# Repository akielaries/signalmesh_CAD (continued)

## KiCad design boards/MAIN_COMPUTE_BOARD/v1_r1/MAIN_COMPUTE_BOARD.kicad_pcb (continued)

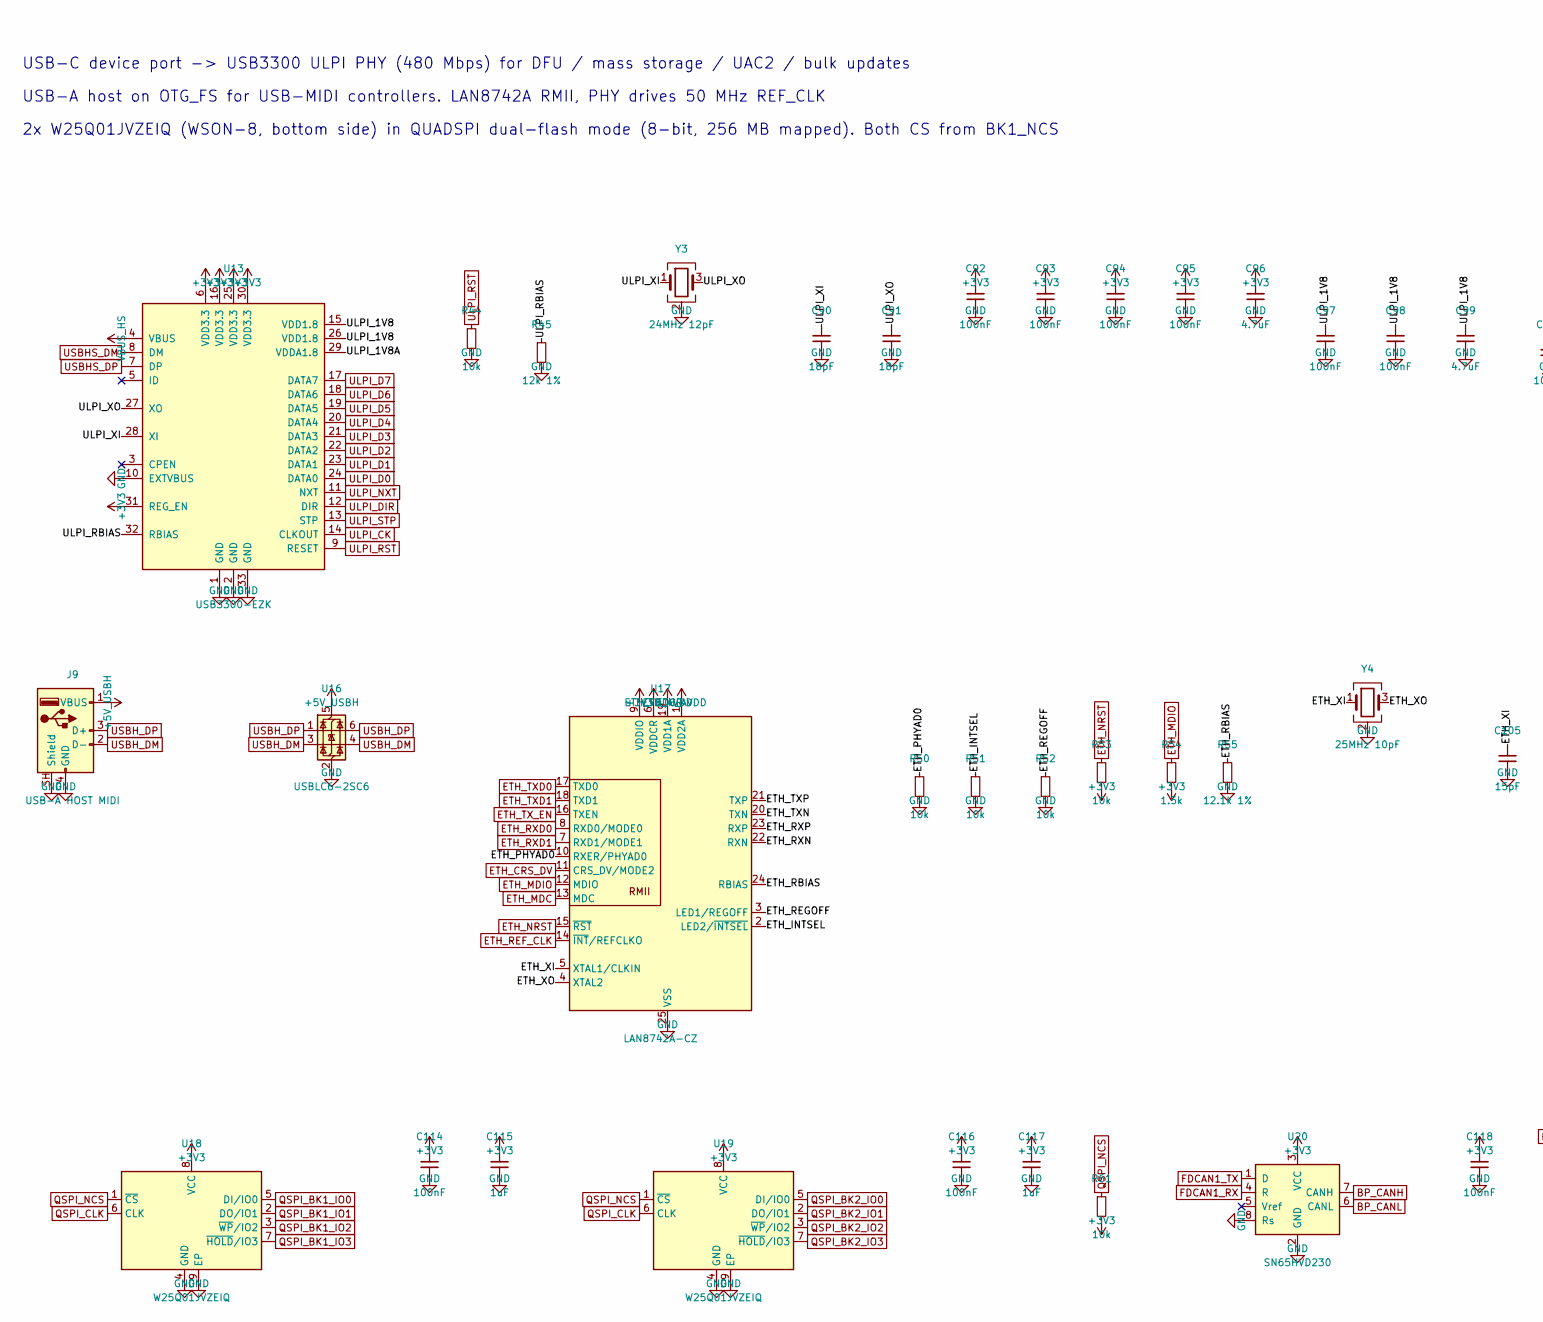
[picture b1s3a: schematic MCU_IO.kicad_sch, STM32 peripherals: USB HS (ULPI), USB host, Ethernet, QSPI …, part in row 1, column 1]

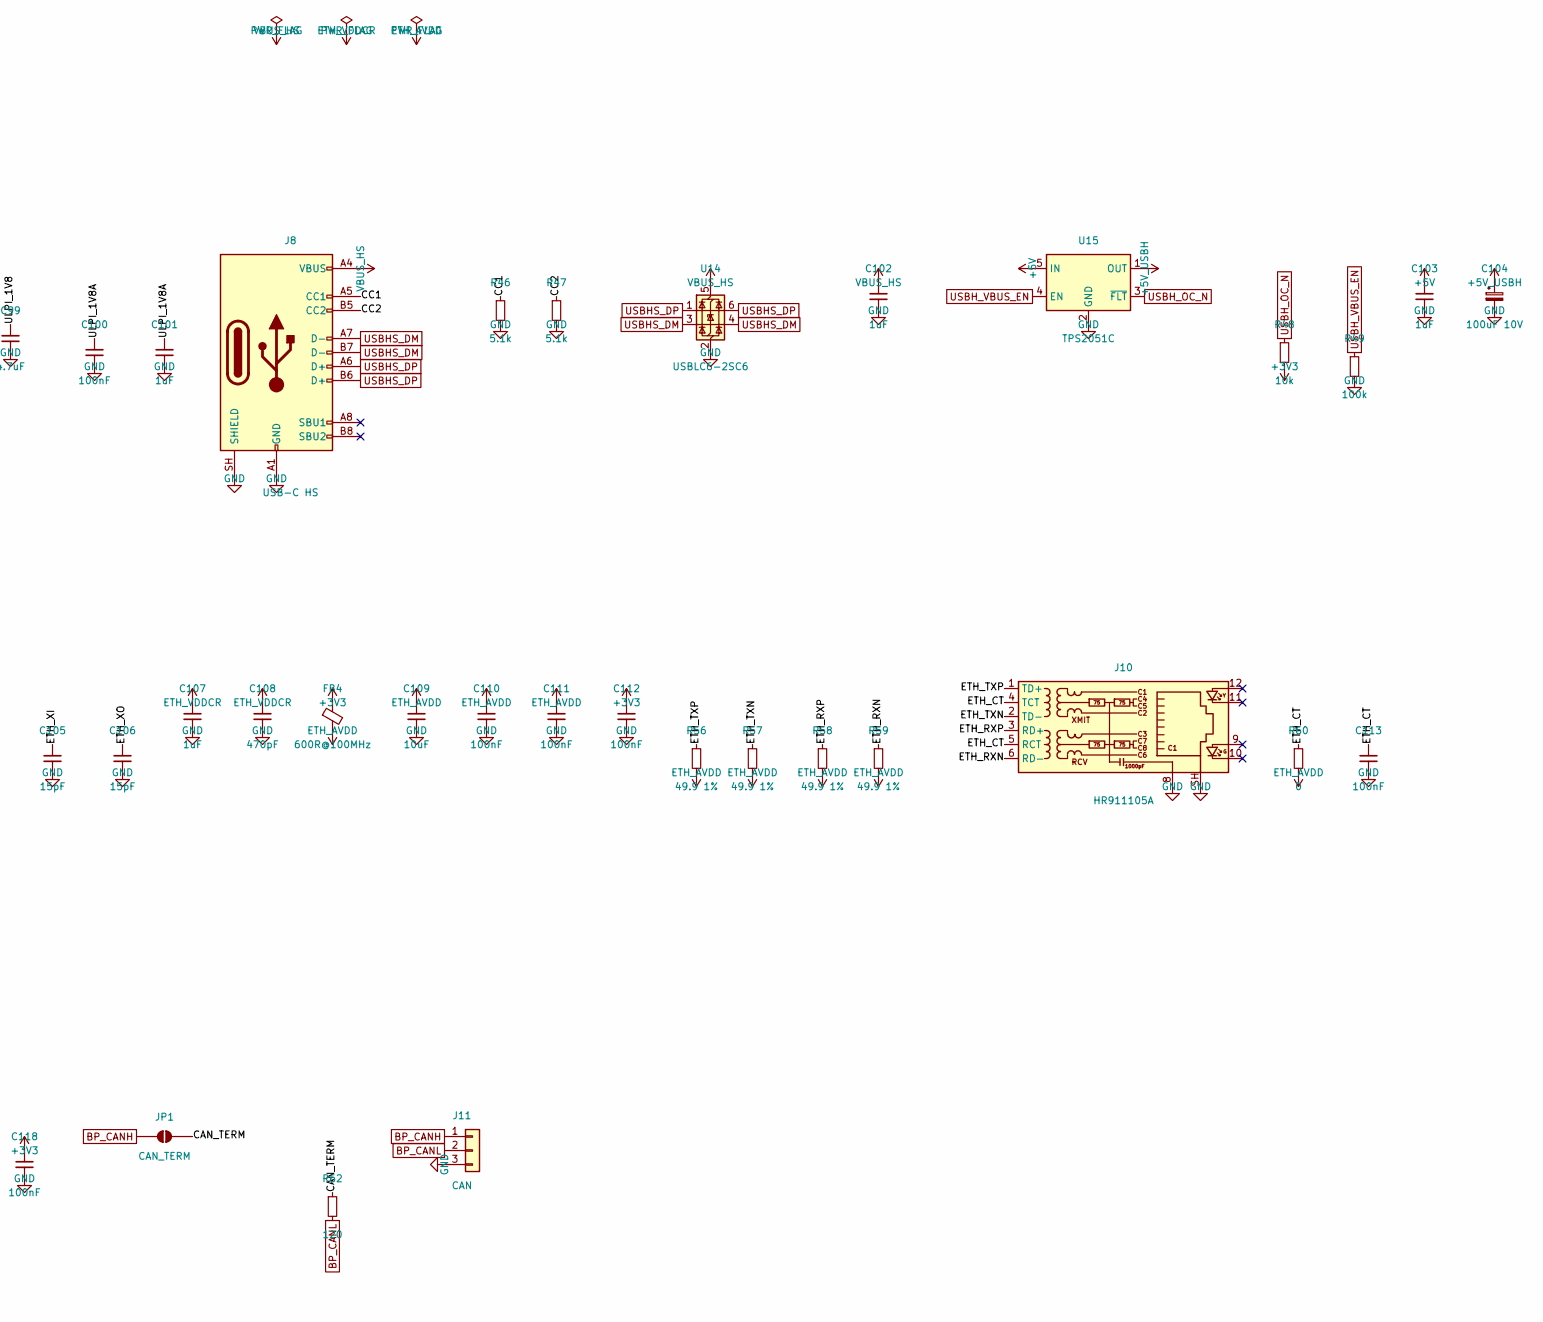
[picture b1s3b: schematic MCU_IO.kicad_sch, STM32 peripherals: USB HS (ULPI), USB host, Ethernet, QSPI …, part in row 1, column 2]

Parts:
C90, C91: 18pF; C_0402_1005Metric
C92, C93, C94, C95, C97, C98, C100, C110, C111, C112, C113, C114, C116, C118: 100nF; C_0402_1005Metric
C96, C99: 4.7uF; C_0603_1608Metric
C101, C102, C103, C107, C115, C117: 1uF; C_0402_1005Metric
C104: 100uF 10V; CP_Elec_6.3x7.7
C105, C106: 15pF; C_0402_1005Metric
C108: 470pF; C_0402_1005Metric
C109: 10uF; C_0805_2012Metric
FB4: 600R@100MHz; L_0603_1608Metric
J8: USB-C HS; USB_C_Receptacle_HRO_TYPE-C-31-M-12
J9: USB-A HOST MIDI; USB_A_Molex_67643_Horizontal
J10: HR911105A; RJ45_Hanrun_HR911105A_Horizontal
J11: CAN; PinHeader_1x03_P2.54mm_Vertical
JP1: CAN_TERM; SolderJumper-2_P1.3mm_Open_RoundedPad1.0x1.5mm
R44, R48, R50, R51, R52, R53, R61: 10k; R_0402_1005Metric
R45: 12k 1%; R_0402_1005Metric
R46, R47: 5.1k; R_0402_1005Metric
R49: 100k; R_0402_1005Metric
R54: 1.5k; R_0402_1005Metric
R55: 12.1k 1%; R_0402_1005Metric
R56, R57, R58, R59: 49.9 1%; R_0402_1005Metric
R60: 0; R_0402_1005Metric
R62: 120; R_0402_1005Metric
U13: USB3300-EZK; QFN-32-1EP_5x5mm_P0.5mm_EP3.45x3.45mm
U14, U16: USBLC6-2SC6; SOT-23-6
U15: TPS2051C; SOT-23-5
U17: LAN8742A-CZ; VQFN-24-1EP_4x4mm_P0.5mm_EP2.5x2.5mm_ThermalVias
U18, U19: W25Q01JVZEIQ; WSON-8-1EP_8x6mm_P1.27mm_EP3.4x4.3mm; LCSC C6926235
U20: SN65HVD230; SOIC-8_3.9x4.9mm_P1.27mm
Y3: 24MHz 12pF; Crystal_SMD_3225-4Pin_3.2x2.5mm
Y4: 25MHz 10pF; Crystal_SMD_3225-4Pin_3.2x2.5mm

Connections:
+3V3: C92.1, C93.1, C94.1, C95.1, C96.1, C112.1, C114.1, C115.1, C116.1, C117.1, C118.1, FB4.1, R48.2, R53.2, R54.2, R61.2, U13.6 (VDD3.3), U13.16 (VDD3.3), U13.25 (VDD3.3), U13.30 (VDD3.3), U13.31 (REG_EN), U17.9 (VDDIO), U18.8 (VCC), U19.8 (VCC), U20.3 (VCC); also elsewhere on the board
+5V: C103.1, U15.5 (IN); also elsewhere on the board
+5V_USBH: C104.1, J9.1 (VBUS), U15.1 (OUT), U16.5 (VBUS)
/MCU_IO/CAN_TERM: JP1.2 (B), R62.1
/MCU_IO/CC1: J8.A5 (CC1), R46.1
/MCU_IO/CC2: J8.B5 (CC2), R47.1
/MCU_IO/ETH_CT: C113.1, J10.4 (TCT), J10.5 (RCT), R60.1
/MCU_IO/ETH_INTSEL: R51.1, U17.2 (LED2/~INTSEL)
/MCU_IO/ETH_PHYAD0: R50.1, U17.10 (RXER/PHYAD0)
/MCU_IO/ETH_RBIAS: R55.1, U17.24 (RBIAS)
/MCU_IO/ETH_REGOFF: R52.1, U17.3 (LED1/REGOFF)
/MCU_IO/ETH_RXN: J10.6 (RD-), R59.1, U17.22 (RXN)
/MCU_IO/ETH_RXP: J10.3 (RD+), R58.1, U17.23 (RXP)
/MCU_IO/ETH_TXN: J10.2 (TD-), R57.1, U17.20 (TXN)
/MCU_IO/ETH_TXP: J10.1 (TD+), R56.1, U17.21 (TXP)
/MCU_IO/ETH_XI: C105.1, U17.5 (XTAL1/CLKIN), Y4.1
/MCU_IO/ETH_XO: C106.1, U17.4 (XTAL2), Y4.3
/MCU_IO/ULPI_1V8: C97.1, C98.1, C99.1, U13.15 (VDD1.8), U13.26 (VDD1.8)
/MCU_IO/ULPI_1V8A: C100.1, C101.1, U13.29 (VDDA1.8)
/MCU_IO/ULPI_RBIAS: R45.1, U13.32 (RBIAS)
/MCU_IO/ULPI_XI: C90.1, U13.28 (XI), Y3.1
/MCU_IO/ULPI_XO: C91.1, U13.27 (XO), Y3.3
BP_CANH: J11.1, JP1.1 (A), U20.7 (CANH); also elsewhere on the board
BP_CANL: J11.2, R62.2, U20.6 (CANL); also elsewhere on the board
ETH_AVDD: C109.1, C110.1, C111.1, FB4.2, R56.2, R57.2, R58.2, R59.2, R60.2, U17.1 (VDD2A), U17.19 (VDD1A)
ETH_CRS_DV: U17.11 (CRS_DV/MODE2); also elsewhere on the board
ETH_MDC: U17.13 (MDC); also elsewhere on the board
ETH_MDIO: R54.1, U17.12 (MDIO); also elsewhere on the board
ETH_NRST: R53.1, U17.15 (~RST); also elsewhere on the board
ETH_REF_CLK: U17.14 (~INT/REFCLKO); also elsewhere on the board
ETH_RXD0: U17.8 (RXD0/MODE0); also elsewhere on the board
ETH_RXD1: U17.7 (RXD1/MODE1); also elsewhere on the board
ETH_TXD0: U17.17 (TXD0); also elsewhere on the board
ETH_TXD1: U17.18 (TXD1); also elsewhere on the board
ETH_TX_EN: U17.16 (TXEN); also elsewhere on the board
ETH_VDDCR: C107.1, C108.1, U17.6 (VDDCR)
FDCAN1_RX: U20.4 (R); also elsewhere on the board
FDCAN1_TX: U20.1 (D); also elsewhere on the board
GND: C90.2, C91.2, C92.2, C93.2, C94.2, C95.2, C96.2, C97.2, C98.2, C99.2, C100.2, C101.2, C102.2, C103.2, C104.2, C105.2, C106.2, C107.2, C108.2, C109.2, C110.2, C111.2, C112.2, C113.2, C114.2, C115.2, C116.2, C117.2, C118.2, J8.A1 (GND), J8.A12 (GND), J8.B1 (GND), J8.B12 (GND), J8.SH (SHIELD), J9.4 (GND), J9.SH (Shield), J10.8, J10.SH, J11.3, R44.2, R45.2, R46.2, R47.2, R49.2, R50.2, R51.2, R52.2, R55.2, U13.1 (GND), U13.2 (GND), U13.10 (EXTVBUS), U13.33 (GND), U14.2 (GND), U15.2 (GND), U16.2 (GND), U17.25 (VSS), U18.4 (GND), U18.9 (EP), U19.4 (GND), U19.9 (EP), U20.2 (GND), U20.8 (Rs), Y3.2 (G), Y3.4 (G), Y4.2 (G), Y4.4 (G); also elsewhere on the board
QSPI_BK1_IO0: U18.5 (DI/IO0); also elsewhere on the board
QSPI_BK1_IO1: U18.2 (DO/IO1); also elsewhere on the board
QSPI_BK1_IO2: U18.3 (~WP/IO2); also elsewhere on the board
QSPI_BK1_IO3: U18.7 (~HOLD/IO3); also elsewhere on the board
QSPI_BK2_IO0: U19.5 (DI/IO0); also elsewhere on the board
QSPI_BK2_IO1: U19.2 (DO/IO1); also elsewhere on the board
QSPI_BK2_IO2: U19.3 (~WP/IO2); also elsewhere on the board
QSPI_BK2_IO3: U19.7 (~HOLD/IO3); also elsewhere on the board
QSPI_CLK: U18.6 (CLK), U19.6 (CLK); also elsewhere on the board
QSPI_NCS: R61.1, U18.1 (~CS), U19.1 (~CS); also elsewhere on the board
ULPI_CK: U13.14 (CLKOUT); also elsewhere on the board
ULPI_D0: U13.24 (DATA0); also elsewhere on the board
ULPI_D1: U13.23 (DATA1); also elsewhere on the board
ULPI_D2: U13.22 (DATA2); also elsewhere on the board
ULPI_D3: U13.21 (DATA3); also elsewhere on the board
ULPI_D4: U13.20 (DATA4); also elsewhere on the board
ULPI_D5: U13.19 (DATA5); also elsewhere on the board
ULPI_D6: U13.18 (DATA6); also elsewhere on the board
ULPI_D7: U13.17 (DATA7); also elsewhere on the board
ULPI_DIR: U13.12 (DIR); also elsewhere on the board
ULPI_NXT: U13.11 (NXT); also elsewhere on the board
ULPI_RST: R44.1, U13.9 (RESET); also elsewhere on the board
ULPI_STP: U13.13 (STP); also elsewhere on the board
USBHS_DM: J8.A7 (D-), J8.B7 (D-), U13.8 (DM), U14.3 (I/O2), U14.4 (I/O2)
USBHS_DP: J8.A6 (D+), J8.B6 (D+), U13.7 (DP), U14.1 (I/O1), U14.6 (I/O1)
USBH_DM: J9.2 (D-), U16.3 (I/O2), U16.4 (I/O2); also elsewhere on the board
USBH_DP: J9.3 (D+), U16.1 (I/O1), U16.6 (I/O1); also elsewhere on the board
USBH_OC_N: R48.1, U15.3 (~FLT); also elsewhere on the board
USBH_VBUS_EN: R49.1, U15.4 (EN); also elsewhere on the board
VBUS_HS: C102.1, J8.A4 (VBUS), J8.A9 (VBUS), J8.B4 (VBUS), J8.B9 (VBUS), U13.4 (VBUS), U14.5 (VBUS)

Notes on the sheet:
USB-C device port -> USB3300 ULPI PHY (480 Mbps) for DFU / mass storage / UAC2 / bulk updates
USB-A host on OTG_FS for USB-MIDI controllers. LAN8742A RMII, PHY drives 50 MHz REF_CLK
2x W25Q01JVZEIQ (WSON-8, bottom side) in QUADSPI dual-flash mode (8-bit, 256 MB mapped). Both CS from BK1_NCS

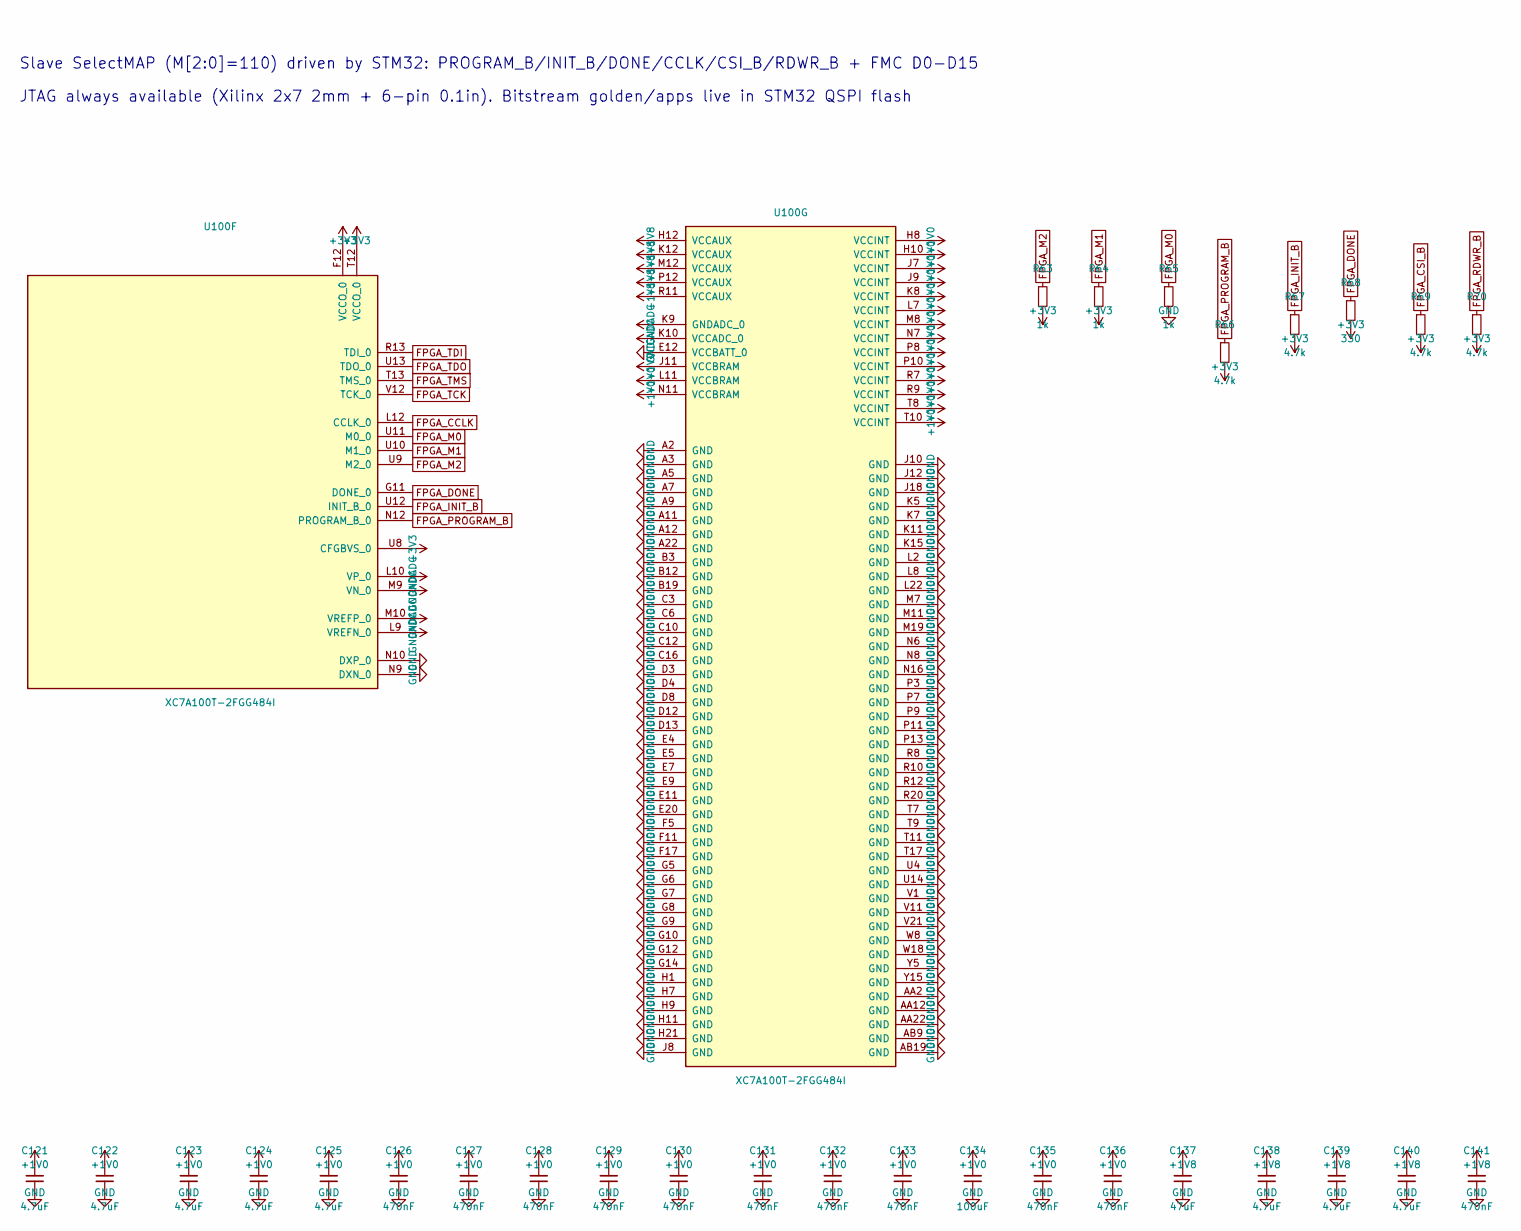
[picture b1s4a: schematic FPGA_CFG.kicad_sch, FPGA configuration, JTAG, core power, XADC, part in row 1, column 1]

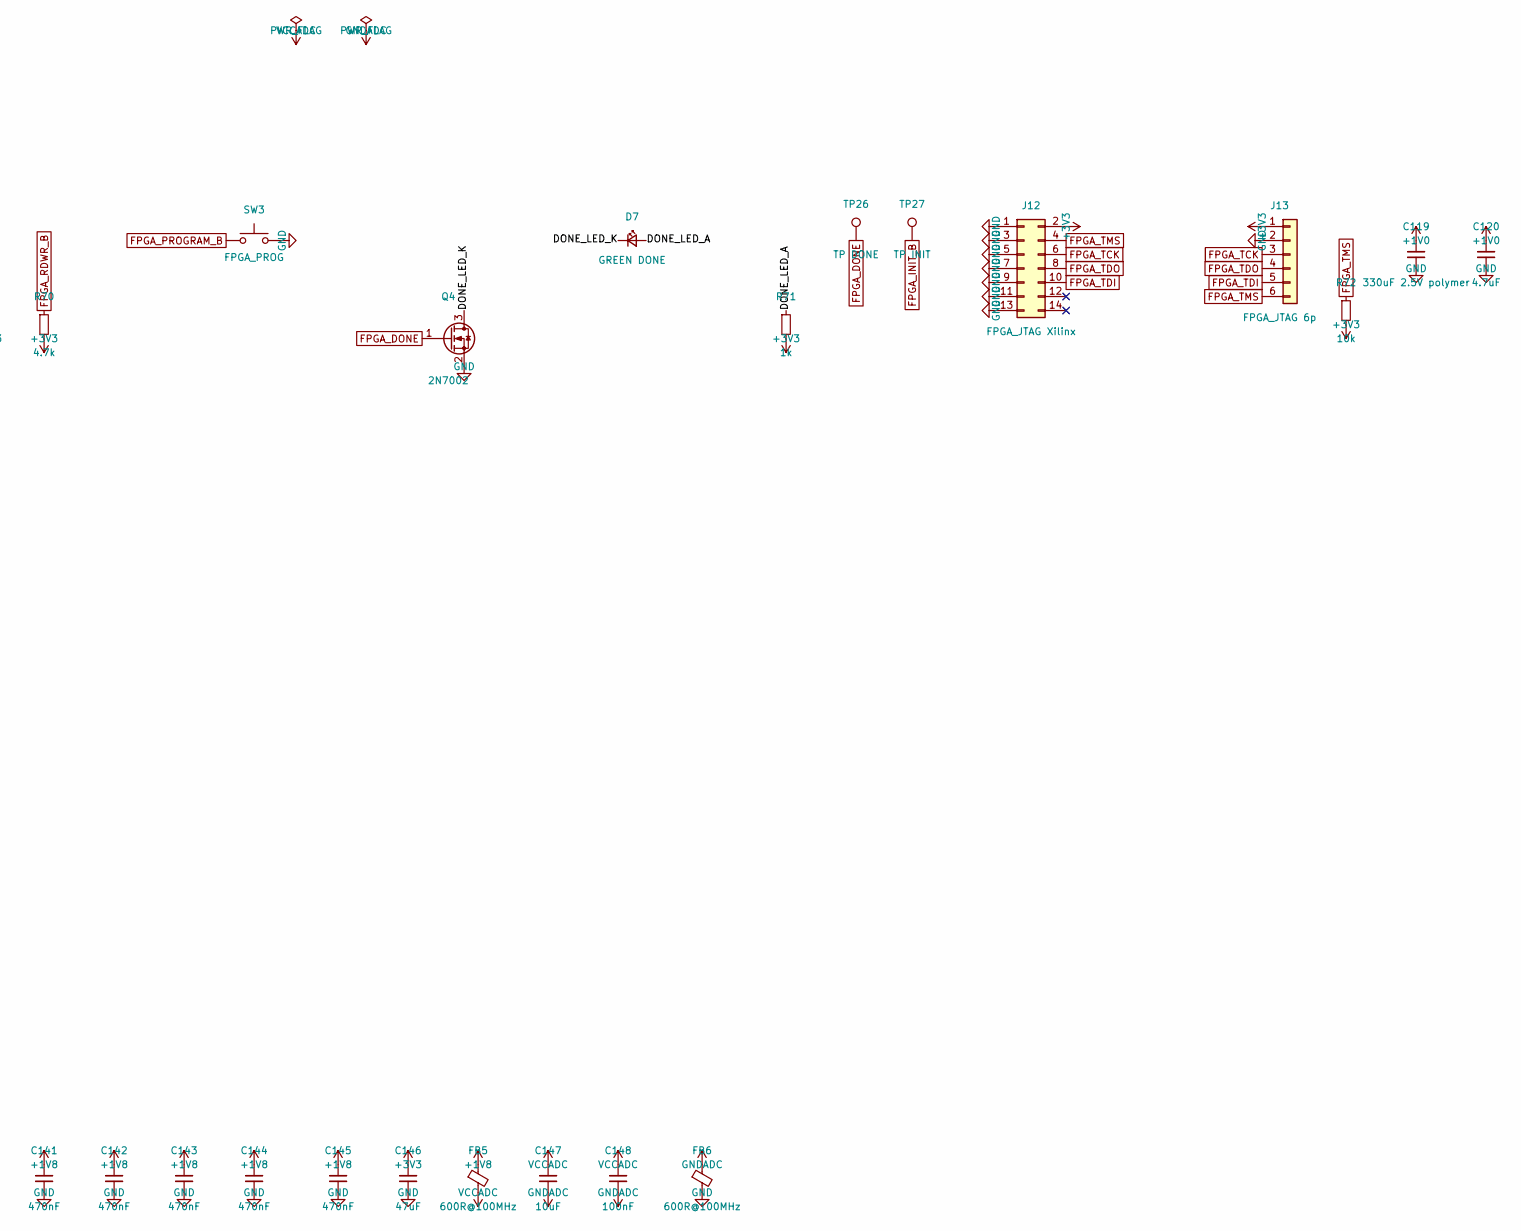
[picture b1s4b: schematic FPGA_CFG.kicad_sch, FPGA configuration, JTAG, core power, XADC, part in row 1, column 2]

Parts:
C119: 330uF 2.5V polymer; CP_EIA-7343-31_Kemet-D
C120, C121, C122, C123, C124, C125, C138, C139, C140: 4.7uF; C_0603_1608Metric
C126, C127, C128, C129, C130, C131, C132, C133, C135, C136, C141, C142, C143, C144, C145: 470nF; C_0402_1005Metric
C134: 100uF; C_1210_3225Metric
C137, C146: 47uF; C_1206_3216Metric
C147: 10uF; C_0805_2012Metric
C148: 100nF; C_0402_1005Metric
D7: GREEN DONE; LED_0603_1608Metric
FB5, FB6: 600R@100MHz; L_0603_1608Metric
J12: FPGA_JTAG Xilinx; PinHeader_2x07_P2.00mm_Vertical
J13: FPGA_JTAG 6p; PinHeader_1x06_P2.54mm_Vertical
Q4: 2N7002; SOT-23
R63, R64, R65, R71: 1k; R_0402_1005Metric
R66, R67, R69, R70: 4.7k; R_0402_1005Metric
R68: 330; R_0402_1005Metric
R72: 10k; R_0402_1005Metric
SW3: FPGA_PROG; SW_SPST_TL3342
TP26: TP DONE; TestPoint_Pad_D1.5mm
TP27: TP INIT; TestPoint_Pad_D1.5mm
U100: XC7A100T-2FGG484I; Xilinx_FGG484

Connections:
+1V0: C119.1, C120.1, C121.1, C122.1, C123.1, C124.1, C125.1, C126.1, C127.1, C128.1, C129.1, C130.1, C131.1, C132.1, C133.1, C134.1, C135.1, C136.1, U100.H8 (VCCINT), U100.H10 (VCCINT), U100.J7 (VCCINT), U100.J9 (VCCINT), U100.J11 (VCCBRAM), U100.K8 (VCCINT), U100.L7 (VCCINT), U100.L11 (VCCBRAM), U100.M8 (VCCINT), U100.N7 (VCCINT), U100.N11 (VCCBRAM), U100.P8 (VCCINT), U100.P10 (VCCINT), U100.R7 (VCCINT), U100.R9 (VCCINT), U100.T8 (VCCINT), U100.T10 (VCCINT); also elsewhere on the board
+1V8: C137.1, C138.1, C139.1, C140.1, C141.1, C142.1, C143.1, C144.1, C145.1, FB5.1, U100.H12 (VCCAUX), U100.K12 (VCCAUX), U100.M12 (VCCAUX), U100.P12 (VCCAUX), U100.R11 (VCCAUX); also elsewhere on the board
+3V3: C146.1, J12.2, J13.1, R63.2, R64.2, R66.2, R67.2, R68.2, R69.2, R70.2, R71.2, R72.2, U100.F12 (VCCO_0), U100.T12 (VCCO_0), U100.U8 (CFGBVS_0); also elsewhere on the board
/FPGA_CFG/DONE_LED_A: D7.2 (A), R71.1
/FPGA_CFG/DONE_LED_K: D7.1 (K), Q4.3 (D)
FPGA_CCLK: U100.L12 (CCLK_0); also elsewhere on the board
FPGA_CSI_B: R69.1; also elsewhere on the board
FPGA_DONE: Q4.1 (G), R68.1, TP26.1, U100.G11 (DONE_0); also elsewhere on the board
FPGA_INIT_B: R67.1, TP27.1, U100.U12 (INIT_B_0); also elsewhere on the board
FPGA_M0: R65.1, U100.U11 (M0_0)
FPGA_M1: R64.1, U100.U10 (M1_0)
FPGA_M2: R63.1, U100.U9 (M2_0)
FPGA_PROGRAM_B: R66.1, SW3.1, U100.N12 (PROGRAM_B_0); also elsewhere on the board
FPGA_RDWR_B: R70.1; also elsewhere on the board
FPGA_TCK: J12.6, J13.3, U100.V12 (TCK_0)
FPGA_TDI: J12.10, J13.5, U100.R13 (TDI_0)
FPGA_TDO: J12.8, J13.4, U100.U13 (TDO_0)
FPGA_TMS: J12.4, J13.6, R72.1, U100.T13 (TMS_0)
GND: C119.2, C120.2, C121.2, C122.2, C123.2, C124.2, C125.2, C126.2, C127.2, C128.2, C129.2, C130.2, C131.2, C132.2, C133.2, C134.2, C135.2, C136.2, C137.2, C138.2, C139.2, C140.2, C141.2, C142.2, C143.2, C144.2, C145.2, C146.2, FB6.2, J12.1, J12.3, J12.5, J12.7, J12.9, J12.11, J12.13, J13.2, Q4.2 (S), R65.2, SW3.2, U100.A2 (GND), U100.A3 (GND), U100.A5 (GND), U100.A7 (GND), U100.A9 (GND), U100.A11 (GND), U100.A12 (GND), U100.A22 (GND), U100.AA2 (GND), U100.AA12 (GND), U100.AA22 (GND), U100.AB9 (GND), U100.AB19 (GND), U100.B3 (GND), U100.B12 (GND), U100.B19 (GND), U100.C3 (GND), U100.C6 (GND), U100.C10 (GND), U100.C12 (GND), U100.C16 (GND), U100.D3 (GND), U100.D4 (GND), U100.D8 (GND), U100.D12 (GND), U100.D13 (GND), U100.E4 (GND), U100.E5 (GND), U100.E7 (GND), U100.E9 (GND), U100.E11 (GND), U100.E12 (VCCBATT_0), U100.E20 (GND), U100.F5 (GND), U100.F11 (GND), U100.F17 (GND), U100.G5 (GND), U100.G6 (GND), U100.G7 (GND), U100.G8 (GND), U100.G9 (GND), U100.G10 (GND), U100.G12 (GND), U100.G14 (GND), U100.H1 (GND), U100.H7 (GND), U100.H9 (GND), U100.H11 (GND), U100.H21 (GND), U100.J8 (GND), U100.J10 (GND), U100.J12 (GND), U100.J18 (GND), U100.K5 (GND), U100.K7 (GND), U100.K11 (GND), U100.K15 (GND), U100.L2 (GND), U100.L8 (GND), U100.L22 (GND), U100.M7 (GND), U100.M11 (GND), U100.M19 (GND), U100.N6 (GND), U100.N8 (GND), U100.N9 (DXN_0), U100.N10 (DXP_0), U100.N16 (GND), U100.P3 (GND), U100.P7 (GND), U100.P9 (GND), U100.P11 (GND), U100.P13 (GND), U100.R8 (GND), U100.R10 (GND), U100.R12 (GND), U100.R20 (GND), U100.T7 (GND), U100.T9 (GND), U100.T11 (GND), U100.T17 (GND), U100.U4 (GND), U100.U14 (GND), U100.V1 (GND), U100.V11 (GND), U100.V21 (GND), U100.W8 (GND), U100.W18 (GND), U100.Y5 (GND), U100.Y15 (GND); also elsewhere on the board
GNDADC: C147.2, C148.2, FB6.1, U100.K9 (GNDADC_0), U100.L9 (VREFN_0), U100.L10 (VP_0), U100.M9 (VN_0), U100.M10 (VREFP_0)
VCCADC: C147.1, C148.1, FB5.2, U100.K10 (VCCADC_0)

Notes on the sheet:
Slave SelectMAP (M[2:0]=110) driven by STM32: PROGRAM_B/INIT_B/DONE/CCLK/CSI_B/RDWR_B + FMC D0-D15
JTAG always available (Xilinx 2x7 2mm + 6-pin 0.1in). Bitstream golden/apps live in STM32 QSPI flash
